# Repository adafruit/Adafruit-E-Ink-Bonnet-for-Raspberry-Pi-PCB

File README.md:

## Adafruit E-Ink Bonnet for Raspberry Pi - 24-pin E-Paper Displays PCB

<a href="http://www.adafruit.com/products/6418"><br/>
Click here to purchase one from the Adafruit shop</a>

PCB files for the Adafruit E-Ink Bonnet for Raspberry Pi - 24-pin E-Paper Displays. 

Format is EagleCAD schematic and board layout
* https://www.adafruit.com/product/6418

### Description

Easy e-paper finally comes to Raspberry Pi, with this bonnet that's designed to make it a breeze to add any 'standard' pinout 24-pin flex-connector E-Ink display. This add-on handles all the extra components needed to make E-Paper interfacing easy for Pi and Pi-compatible boards. We even include extras like two user buttons, Stemma QT I2C port, and a 3W I2S speaker so you can also have audio playback. Insert your favorite E-Paper display to the connector and you'll have a powerful Linux-powered display for your desk or wall.

Chances are you've seen one of those new-fangled 'e-readers' like the Kindle or Nook. They have gigantic electronic paper 'static' displays - that means the image stays on the display even when power is completely disconnected. The image is also high contrast and very daylight readable. It really does look just like printed paper!

<b>Please note that this does NOT come with the raw display itself</b> - [we stock a wide variety of bare displays](https://www.adafruit.com/product/6396) that will work great. Don't forget to verify that each display needs driver code to match the driver chip. For displays we sell, [we have examples in our E-Ink Python library you can use to craft your own project.](https://github.com/adafruit/Adafruit_CircuitPython_EPD) Often times the E-Paper display has a short cable, in which case [we suggest one of our extender cables.](https://www.adafruit.com/product/4230)

<b>Comes completely pre-assembled and tested</b> so you can plug it in and install our Python code! <b>Works with any Raspberry Pi computer that has a 2x20 connector</b>, such as the Pi B+, Pi 2, Pi 3, Pi 4, Pi 5, and Pi Zero (and any others that have a 2x20 connector!) For installing on Pi's where you need to clear a case or you don't want it against the board, [grab a 2x20 socket riser.](https://www.adafruit.com/product/4079)

Since we had some space on the bonnet we added a [MAX98357 3W 4-8Ω speaker driver](https://www.adafruit.com/product/3006) which has digital I2S input for great sounding audio. This makes it easy to add audio alerts and feedback to your E-Paper projects. [Note you'll have to add a 4-8Ω speaker to the terminal blocks.](https://www.adafruit.com/product/4445)

[On the bottom, we have a Qwiic/STEMMA QT connector for I2C sensors and devices so you can plug and play any of our STEMMA QT devices.](https://www.adafruit.com/?q=stemma%20qt)

<b>To summarize, you will probably want some accessories to build a full project:</b>

* A matching 'bare' E-Paper display with standard 24-pin connector [we stock a wide variety of bare displays here](https://www.adafruit.com/product/6396)
* [One of our extender cables](https://www.adafruit.com/product/4230) so you have plenty of maneuvering room
* [A 4-8Ω speaker](https://www.adafruit.com/product/4445) if you want to use the onboard amplifier
* And of course a Raspberry Pi or other 2x20-connector'd single-board Linux computer!

### License

Adafruit invests time and resources providing this open source design, please support Adafruit and open-source hardware by purchasing products from [Adafruit](https://www.adafruit.com)!

Designed by Limor Fried/Ladyada for Adafruit Industries.

Creative Commons Attribution/Share-Alike, all text above must be included in any redistribution. 
See license.txt for additional details.

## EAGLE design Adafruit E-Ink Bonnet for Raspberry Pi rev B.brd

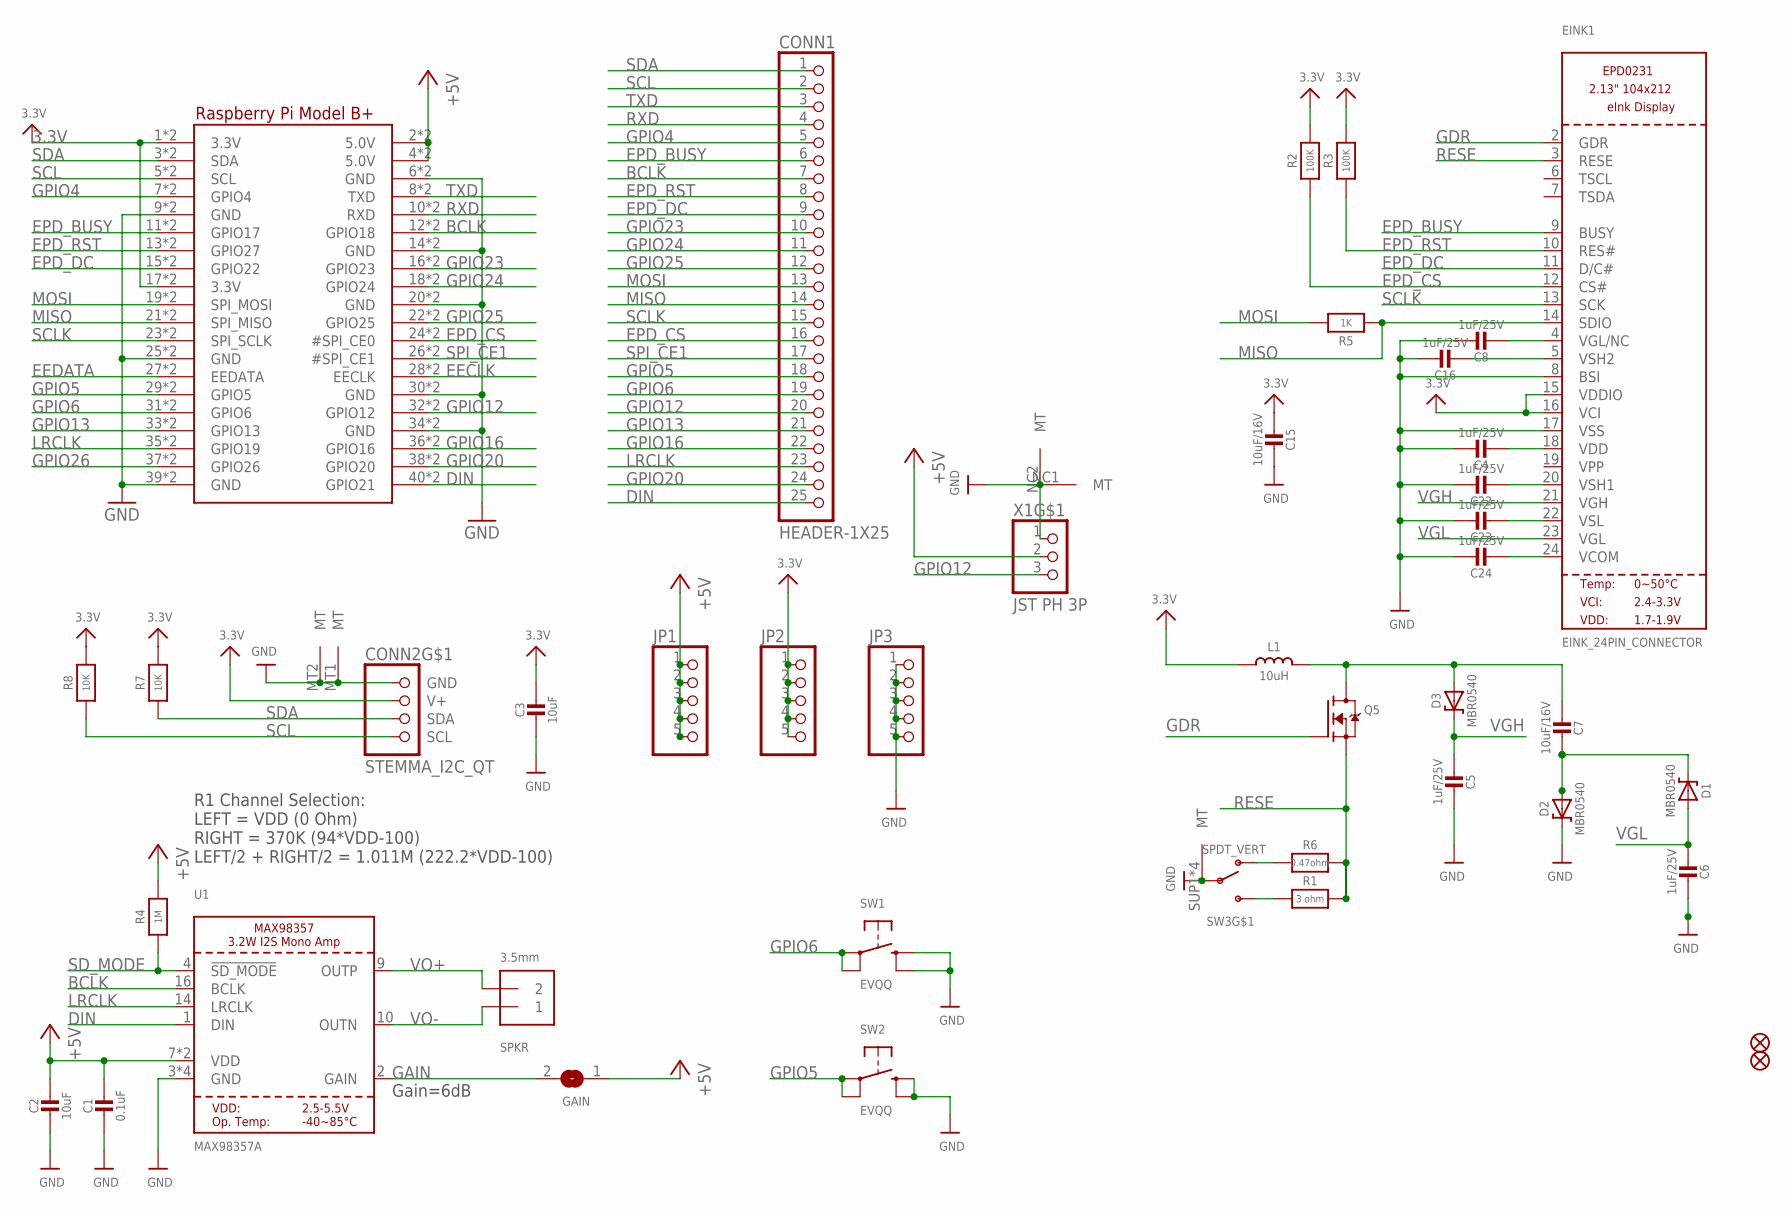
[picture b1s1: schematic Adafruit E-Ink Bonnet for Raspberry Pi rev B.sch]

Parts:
C1: 0.1uF; 0603-NO
C2, C3: 10uF; 0805-NO
C4, C5, C6, C8, C16, C22, C23, C24: 1uF/25V; 0603-NO
C7, C15: 10uF/16V; 0805-NO
CONN1: HEADER-1X25; 1X25_ROUND_70MIL
CONN2: STEMMA_I2C_QT; JST_SH4
D1, D2, D3: MBR0540; SOD-123
EINK1: EINK_24PIN_CONNECTOR; EINK_24PIN
FID2, FID3: FIDUCIAL_1MM
GAIN: SOLDERJUMPERCLOSED; SOLDERJUMPER_CLOSEDWIRE
JP1, JP2, JP3: HEADER-1X576MIL; 1X05_ROUND_76
L1: 10uH; INDUCTOR_4X4MM_NR401
Q5: IRLML0100; SOT23-3
R1: 3 ohm; 0603-NO
R2, R3: 100K; 0603-NO
R4: 1M; 0603-NO
R5: 1K; 0603-NO
R6: 0.47ohm; 0603-NO
R7, R8: 10K; 0603-NO
RPI1: RASPBERRYPI_BPLUS_BONNET_THMSMT; PI_BONNET_THMSMT
SPKR: 3.5mm; TERMBLOCK_1X2-3.5MM
SW1, SW2: EVQQ; 6MMX6MM_TACTILE_SMT
SW3: SPDT_VERT; SPDT_SMT_SSSS811101
U1: MAX98357A; QFN16_3MM
X1: JST PH 3P; JSTPH3

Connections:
3.3V: C3.1, C15.2, CONN2.2 (V+), EINK1.15 (VDDIO), EINK1.16 (VCI), JP2.1, JP2.2, JP2.3, JP2.4, JP2.5, L1.P$2 (2), R2.2, R3.2, R7.1, R8.1, RPI1.1 (3.3V), RPI1.17 (3.3V), RPI1.S1 (3.3V), RPI1.S17 (3.3V)
+5V: C1.1, C2.1, GAIN.1, JP1.1, JP1.2, JP1.3, JP1.4, JP1.5, R4.2, RPI1.2 (5.0V), RPI1.4 (5.0V), RPI1.S2 (5.0V), RPI1.S4 (5.0V), U1.7 (VDD), U1.8 (VDD), X1.2
BCLK: CONN1.7, RPI1.12 (GPIO18), RPI1.S12 (GPIO18), U1.16 (BCLK)
DIN: CONN1.25, RPI1.40 (GPIO21), RPI1.S40 (GPIO21), U1.1 (DIN)
EECLK: RPI1.28 (EECLK), RPI1.S28 (EECLK)
EEDATA: RPI1.27 (EEDATA), RPI1.S27 (EEDATA)
EPD_BUSY: CONN1.6, EINK1.9 (BUSY), RPI1.11 (GPIO17), RPI1.S11 (GPIO17)
EPD_CS: CONN1.16, EINK1.12 (CS#), R2.1, RPI1.24 (#SPI_CE0), RPI1.S24 (#SPI_CE0)
EPD_DC: CONN1.9, EINK1.11 (D/C#), RPI1.15 (GPIO22), RPI1.S15 (GPIO22)
EPD_RST: CONN1.8, EINK1.10 (RES#), R3.1, RPI1.13 (GPIO27), RPI1.S13 (GPIO27)
GAIN: GAIN.2, U1.2 (GAIN)
GDR: EINK1.2 (GDR), Q5.1 (G)
GND: C1.2, C2.2, C3.2, C4.1, C5.2, C6.2, C8.1, C15.1, C16.1, C22.1, C23.1, C24.1, CONN2.1 (GND), CONN2.MT1 (MT), CONN2.MT2 (MT), D2.C, EINK1.8 (BSI), EINK1.17 (VSS), JP3.1, JP3.2, JP3.3, JP3.4, JP3.5, RPI1.6 (GND), RPI1.9 (GND), RPI1.14 (GND), RPI1.20 (GND), RPI1.25 (GND), RPI1.30 (GND), RPI1.34 (GND), RPI1.39 (GND), RPI1.S6 (GND), RPI1.S9 (GND), RPI1.S14 (GND), RPI1.S20 (GND), RPI1.S25 (GND), RPI1.S30 (GND), RPI1.S34 (GND), RPI1.S39 (GND), SW1.B (S), SW1.B' (S1), SW2.B (S), SW2.B' (S1), SW3.B, SW3.SUP1 (MT), SW3.SUP2 (MT), SW3.SUP3 (MT), SW3.SUP4 (MT), U1.3 (GND), U1.11 (GND), U1.15 (GND), U1.THERMAL (GND), X1.1, X1.NC1 (MT), X1.NC2 (MT)
GPIO4: CONN1.5, RPI1.7 (GPIO4), RPI1.S7 (GPIO4)
GPIO5: CONN1.18, RPI1.29 (GPIO5), RPI1.S29 (GPIO5), SW2.A, SW2.A' (P1)
GPIO6: CONN1.19, RPI1.31 (GPIO6), RPI1.S31 (GPIO6), SW1.A, SW1.A' (P1)
GPIO12: CONN1.20, RPI1.32 (GPIO12), RPI1.S32 (GPIO12), X1.3
GPIO13: CONN1.21, RPI1.33 (GPIO13), RPI1.S33 (GPIO13)
GPIO16: CONN1.22, RPI1.36 (GPIO16), RPI1.S36 (GPIO16)
GPIO20: CONN1.24, RPI1.38 (GPIO20), RPI1.S38 (GPIO20)
GPIO23: CONN1.10, RPI1.16 (GPIO23), RPI1.S16 (GPIO23)
GPIO24: CONN1.11, RPI1.18 (GPIO24), RPI1.S18 (GPIO24)
GPIO25: CONN1.12, RPI1.22 (GPIO25), RPI1.S22 (GPIO25)
GPIO26: RPI1.37 (GPIO26), RPI1.S37 (GPIO26)
LRCLK: CONN1.23, RPI1.35 (GPIO19), RPI1.S35 (GPIO19), U1.14 (LRCLK)
MISO: CONN1.14, EINK1.14 (SDIO), R5.1, RPI1.21 (SPI_MISO), RPI1.S21 (SPI_MISO)
MOSI: CONN1.13, R5.2, RPI1.19 (SPI_MOSI), RPI1.S19 (SPI_MOSI)
unnamed: R1.2, SW3.C (S)
unnamed: C7.2, D1.C, D2.A
unnamed: C7.1, D3.A, L1.P$1 (1), Q5.3 (D)
unnamed: C16.2, EINK1.5 (VSH2)
unnamed: C4.2, EINK1.18 (VDD)
unnamed: C22.2, EINK1.20 (VSH1)
unnamed: R6.2, SW3.A (O)
unnamed: C8.2, EINK1.4 (VGL/NC)
unnamed: C23.2, EINK1.22 (VSL)
unnamed: C24.2, EINK1.24 (VCOM)
RESE: EINK1.3 (RESE), Q5.2 (S), R1.1, R6.1
RXD: CONN1.4, RPI1.10 (RXD), RPI1.S10 (RXD)
SCL: CONN1.2, CONN2.4 (SCL), R8.2, RPI1.5 (SCL), RPI1.S5 (SCL)
SCLK: CONN1.15, EINK1.13 (SCK), RPI1.23 (SPI_SCLK), RPI1.S23 (SPI_SCLK)
SDA: CONN1.1, CONN2.3 (SDA), R7.2, RPI1.3 (SDA), RPI1.S3 (SDA)
SD_MODE: R4.1, U1.4 (!SD_MODE)
SPI_CE1: CONN1.17, RPI1.26 (#SPI_CE1), RPI1.S26 (#SPI_CE1)
TXD: CONN1.3, RPI1.8 (TXD), RPI1.S8 (TXD)
VGH: C5.1, D3.C, EINK1.21 (VGH)
VGL: C6.1, D1.A, EINK1.23 (VGL)
VO+: SPKR.2, U1.9 (OUTP)
VO-: SPKR.1, U1.10 (OUTN)

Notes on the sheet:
R1 Channel Selection: LEFT = VDD (0 Ohm) RIGHT = 370K (94*VDD-100) LEFT/2 + RIGHT/2 = 1.011M (222.2*VDD-100)
Gain=6dB

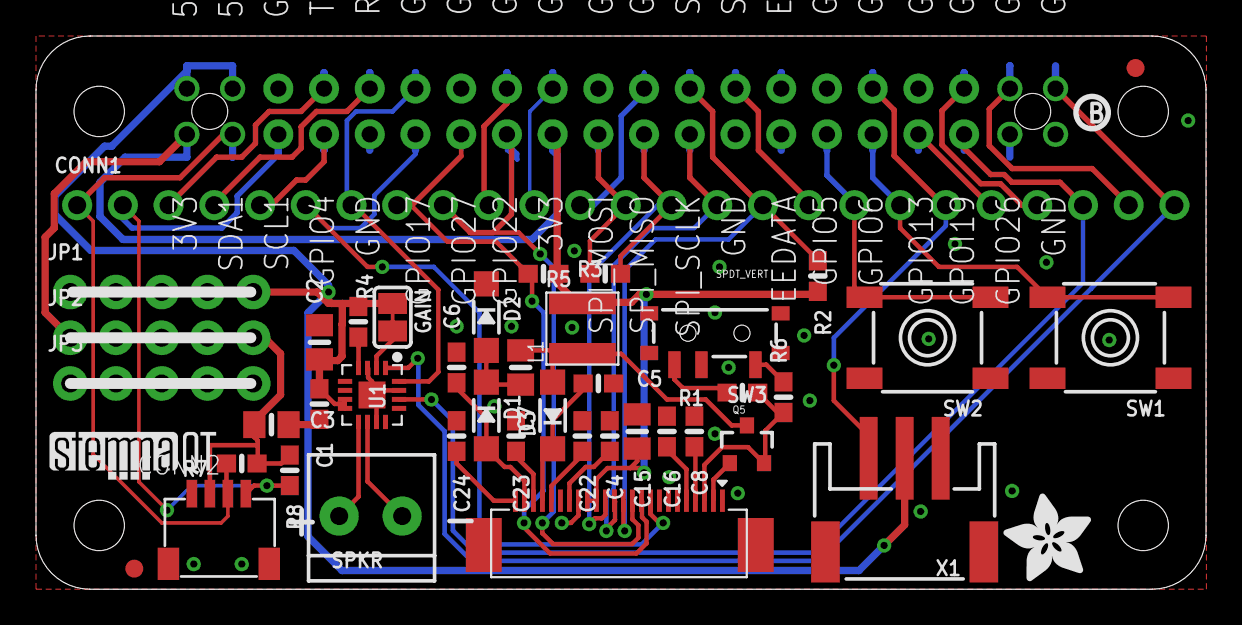
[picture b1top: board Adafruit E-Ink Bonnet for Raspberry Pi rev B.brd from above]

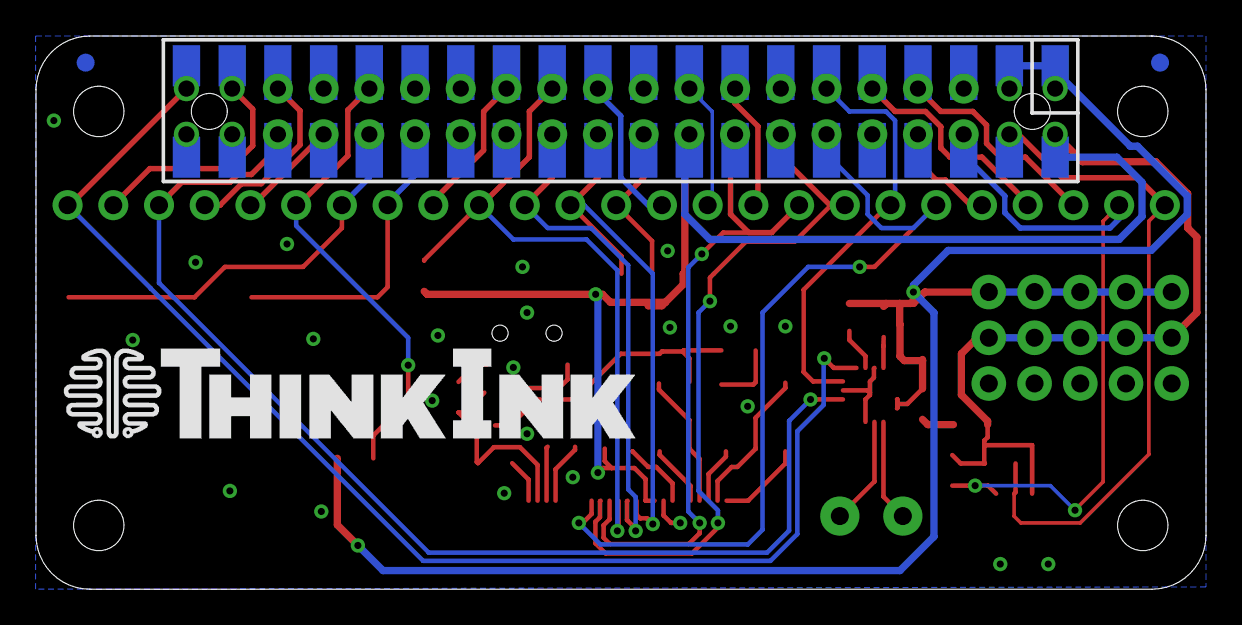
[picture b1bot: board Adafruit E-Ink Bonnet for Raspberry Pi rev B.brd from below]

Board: 2 copper layers, 65.0 x 30.7 mm, 85 parts (4 on the bottom side), 49 nets.

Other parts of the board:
E$1: THINKINK_1.25IN
PLABEL0: PLABEL0
PLABEL1: PLABEL1
PLABEL2: PLABEL2
PLABEL3: PLABEL3
PLABEL4: PLABEL4
PLABEL5: PLABEL5
PLABEL6: PLABEL6
PLABEL7: PLABEL7
PLABEL8: PLABEL8
PLABEL9: PLABEL9
PLABEL10: PLABEL10
PLABEL11: PLABEL11
PLABEL12: PLABEL12
PLABEL13: PLABEL13
PLABEL14: PLABEL14
PLABEL15: PLABEL15
PLABEL16: PLABEL16
PLABEL17: PLABEL17
PLABEL18: PLABEL18
PLABEL19: PLABEL19
PLABEL20: PLABEL20
PLABEL21: PLABEL21
PLABEL22: PLABEL22
PLABEL23: PLABEL23
PLABEL24: PLABEL24
PLABEL25: PLABEL25
PLABEL26: PLABEL26
PLABEL27: PLABEL27
PLABEL28: PLABEL28
PLABEL29: PLABEL29
PLABEL30: PLABEL30
PLABEL31: PLABEL31
PLABEL32: PLABEL32
PLABEL33: PLABEL33
PLABEL34: PLABEL34
PLABEL35: PLABEL35
PLABEL36: PLABEL36
PLABEL37: PLABEL37
PLABEL38: PLABEL38
U$11: PCBFEAT-REV-040
U$12: ADAFRUIT_5MM
U$24: STEMMAQT

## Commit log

2025-09-16 cookiecutter

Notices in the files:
parts and their libraries:
microbuilder: This work is placed in the public domain, and may be freely used for commercial and non-commercial work with the following conditions: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
